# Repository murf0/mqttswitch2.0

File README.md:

**mqttSwitch2.0**
==========
**Features:**

ESP8266
* Status of GPIO pins as published mqtt-message
* Capability of esp sent on boot to mqtt broker
* Set status of GPIO pin (on-off for now) via MQtt Message (Set at compiletime capabilities)
* WifiManager with Mqtt settings available
* OTA prepared (For boards with more than 4mbit memory)
* Mangled version of [MQTT library for the ESP8266 ](https://github.com/tuanpmt/esp_mqtt) library included. Will now work with Arduino ESP8266 SDK. (after a slight mod to platform.txt)
* Mqtt with SSL enabled only
* Mqtt with username + password

HTML
* Java-script enabled interface to control multiple switches. Uses Getvariables for username/password
* Nice-name for each switch configured here
* No webserver required everything is handled in web-browser

OTA Firmwarecheck
* php required, script included based on the standard examples.

**Installation**
(Instructions for macOS)

* edit: ~/Library/Arduino15/packages/esp8266/hardware/esp8266/2.3.0 platform.txt  add "-lssl --allow-multiple-definition" to the end of the Linker row. (the row begins with compiler.c.elf.libs=)
See http://www.delorie.com/gnu/docs/binutils/ld_3.html for information. The linker uses the first found definition)
* symlink in Mqtt library "ln -s $(pwd)/lib/mqtt ~/Documents/Arduino/libraries/mqtt" or move it there
***Libraries used***
* [MQTT library for the ESP8266 ](https://github.com/tuanpmt/esp_mqtt) By Tuanpmt (thanks!) (This is included in the repo for use by Arduino ESP8266) (MIT-License)
* [WifiManager library for the ESP8266 ](https://github.com/tzapu/WiFiManager#install-through-library-manager) By Tzapu (MIT-License)
* [ArduinoJson library for Arduino](https://github.com/bblanchon/ArduinoJson) (MIT-License)

**Hardware**
(This description is a mess sorry, please see included eagle files)
GPIO2 is connected to the base of a NPN3906 transistor via a 1k resistor. Collector is conneted to Ground, Emittor is connected to the Relay. the Groound of relay to 5.0v (USB)
ESP8266 -03, GPIO 15 via 10k resistor to ground, CH_PD via 10k resistor to VCC 3.3v regulator AMS1117 connected to VCC5.0

***Schematic***

***Board***

**Author:**
[Mikael "Murf" Mellgren](https://murf.se)

**LICENSE - "BSD"**
mqttSwitch2.0: Copyright (c) 2017 Mikael MURF Mellgren , https://murf.se

Redistribution and use in source and binary forms, with or without modification, are permitted provided that the following conditions are met:

1. Redistributions of source code must retain the above copyright notice, this list of conditions and the following disclaimer.

2. Redistributions in binary form must reproduce the above copyright notice, this list of conditions and the following disclaimer in the documentation and/or other materials provided with the distribution.

THIS SOFTWARE IS PROVIDED BY THE COPYRIGHT HOLDERS AND CONTRIBUTORS "AS IS" AND ANY EXPRESS OR IMPLIED WARRANTIES, INCLUDING, BUT NOT LIMITED TO, THE IMPLIED WARRANTIES OF MERCHANTABILITY AND FITNESS FOR A PARTICULAR PURPOSE ARE DISCLAIMED. IN NO EVENT SHALL THE COPYRIGHT HOLDER OR CONTRIBUTORS BE LIABLE FOR ANY DIRECT, INDIRECT, INCIDENTAL, SPECIAL, EXEMPLARY, OR CONSEQUENTIAL DAMAGES (INCLUDING, BUT NOT LIMITED TO, PROCUREMENT OF SUBSTITUTE GOODS OR SERVICES; LOSS OF USE, DATA, OR PROFITS; OR BUSINESS INTERRUPTION) HOWEVER CAUSED AND ON ANY THEORY OF LIABILITY, WHETHER IN CONTRACT, STRICT LIABILITY, OR TORT (INCLUDING NEGLIGENCE OR OTHERWISE) ARISING IN ANY WAY OUT OF THE USE OF THIS SOFTWARE, EVEN IF ADVISED OF THE POSSIBILITY OF SUCH DAMAGE.

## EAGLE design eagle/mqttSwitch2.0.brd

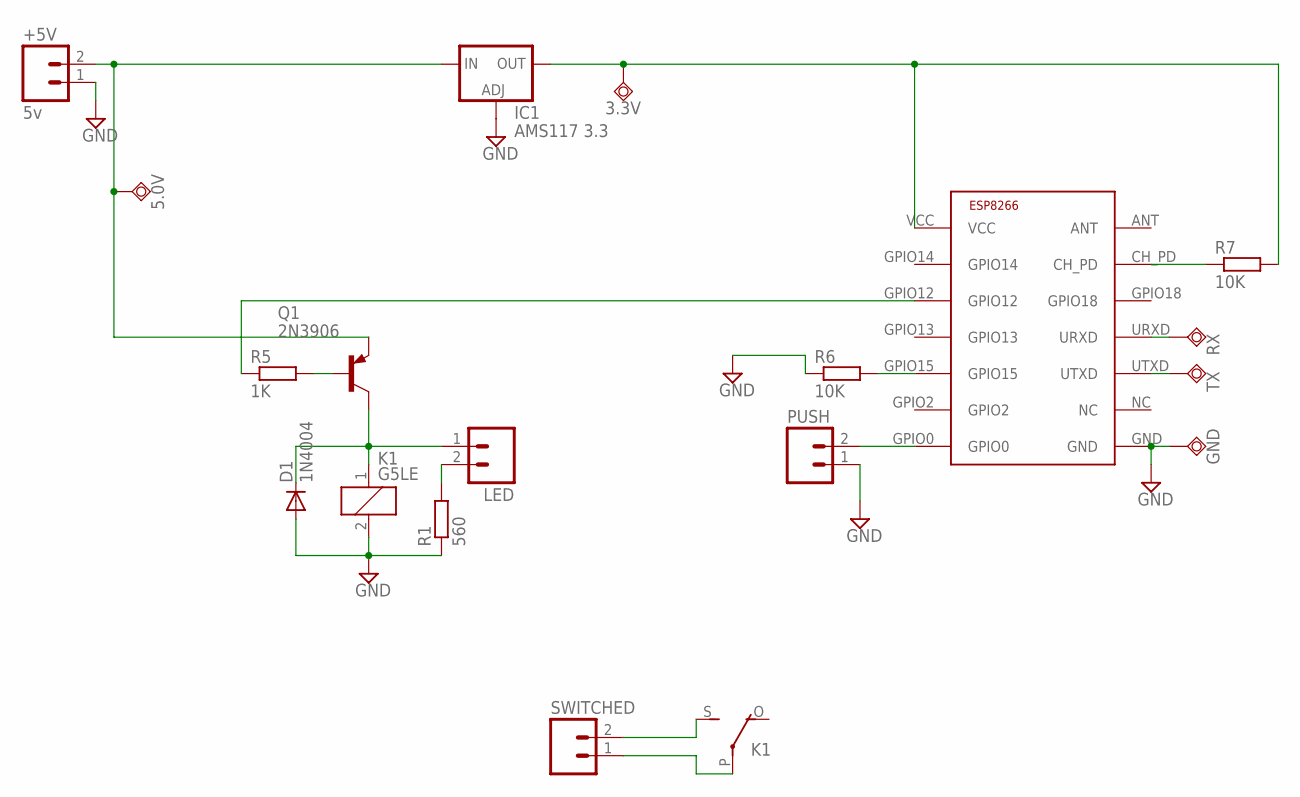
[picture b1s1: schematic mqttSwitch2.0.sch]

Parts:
3.3V, 5.0V: TPSQTP19R; TP19R
+5V: 5v; 1X02
D1: 1N4004; DO41-10
GND: TPSQTP19R; TP19R
IC1: AMS117 3.3; SOT223
K1: G5LE
LED: M02PTH; 1X02
PUSH: M02PTH; 1X02
Q1: 2N3906; TO92
R1: 560; R0805
R5: 1K; R0805
R6, R7: 10K; R0805
RX: TPSQTP19R; TP19R
SWITCHED: M02PTH4; 1X02_XTRA_BIG
TX: TPSQTP19R; TP19R
U$1: ESP8266; ESP-03

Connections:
GND: +5V.1, D1.A, GND.TP, IC1.1 (ADJ), K1.2, PUSH.1, R1.1, R6.1, U$1.GND
unnamed: RX.TP, U$1.URXD
unnamed: R7.1, U$1.CH_PD
unnamed: 3.3V.TP, IC1.4 (OUT), R7.2, U$1.VCC
unnamed: 5.0V.TP, +5V.2, IC1.3 (IN), Q1.3 (E)
unnamed: Q1.2 (B), R5.2
unnamed: R6.2, U$1.GPIO15
unnamed: D1.C, K1.1, LED.1, Q1.1 (C)
unnamed: TX.TP, U$1.UTXD
unnamed: PUSH.2, U$1.GPIO0
unnamed: K1.P, SWITCHED.1
unnamed: LED.2, R1.2
unnamed: R5.1, U$1.GPIO12
unnamed: K1.S, SWITCHED.2

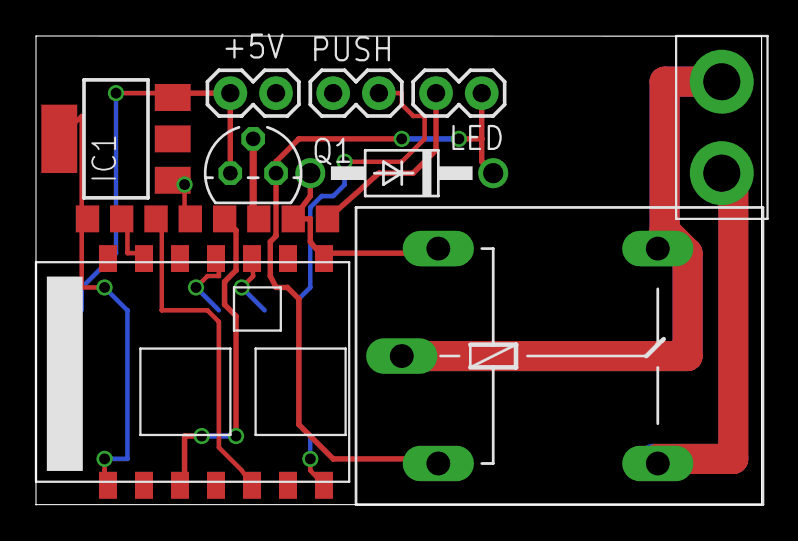
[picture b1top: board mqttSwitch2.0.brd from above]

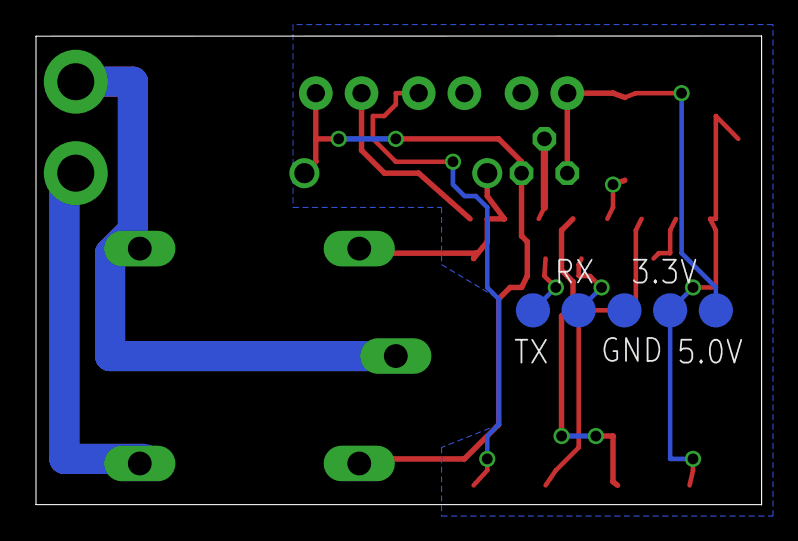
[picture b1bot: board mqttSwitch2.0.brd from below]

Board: 2 copper layers, 40.3 x 26.0 mm, 18 parts (5 on the bottom side), 14 nets.

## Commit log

2016-10-26 First commit, Working
2016-11-06 Fixed and usable
2016-12-31 Updated to get status on load, added status
2017-01-13 Updated ignorefile, and index with markers for status
2017-01-25 Updated to NPN, Started on KiCad
2017-01-26 Removed NPN nonsense, Does not work USE PNP 2n3906
2017-02-02 Latest
2017-02-02 Updated License

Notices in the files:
parts and their libraries:
SparkFun-Connectors: Licensing: Creative Commons ShareAlike 4.0 International - https://creativecommons.org/licenses/by-sa/4.0
